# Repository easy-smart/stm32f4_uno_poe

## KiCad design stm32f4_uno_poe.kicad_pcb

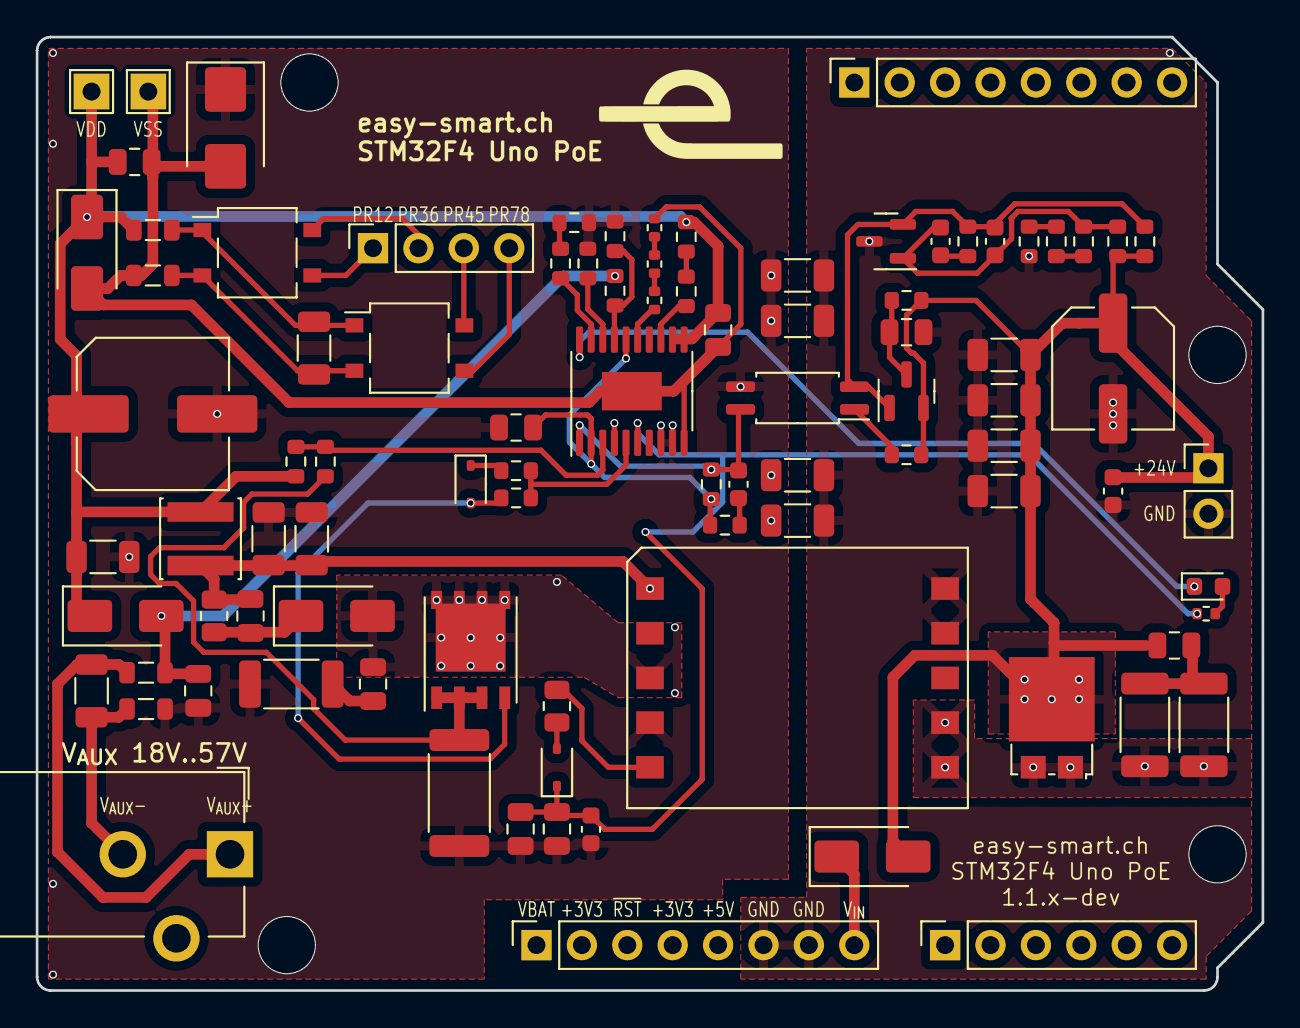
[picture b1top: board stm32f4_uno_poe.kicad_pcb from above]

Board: 2 copper layers, 68.6 x 53.3 mm, 95 parts (0 on the bottom side), 50 nets.

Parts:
C201, C228: 1u 50V; C_0805_2012Metric
C202: 47n 50V; C_0603_1608Metric
C203, C209, C217, C218, C220, C221: 1n 2kV; C_1206_3216Metric
C204, C210, C215, C225, C229: 100n 100V; C_0805_2012Metric
C205: 100p 50V; C_0603_1608Metric
C206: 22n 50V; C_0603_1608Metric
C207, C213, C214: 2u2 100V; C_1206_3216Metric
C211: 47u 63V; C_Elec_8x10.2
C216: 100p 500V; C_0805_2012Metric
C219, C232: 1u 50V; C_0603_1608Metric
C222: 330p 500V; C_0805_2012Metric
C223, C224, C226, C230: 4u7 50V; C_1206_3216Metric
C227: 22u 25V; C_0805_2012Metric
C231: 22u 63V; C_Elec_6.3x5.4
D101: SS210; D_SMA
D201: BAT54S; SOT-23
D202: SS220; D_SMA
D203, D204: MB10S; TO-269AA
D205: 1A 1kV 75ns; D_SMA
D206, D207: 1N4148WS; D_SOD-323
D208: 150V 10A; TO-277A
D209: 58V TVS; D_SMB
D210: LED green; LED_0603_1608Metric
D214: 58V TVS; D_SMA
J106: Power; PinSocket_1x08_P2.54mm_Vertical
J107: Conn_01x04; PinSocket_1x04_P2.54mm_Vertical
J109: STM32 GPIO; PinSocket_1x06_P2.54mm_Vertical
J110: Digital/PWM; PinSocket_1x08_P2.54mm_Vertical
J112: Barrel_Jack; CUI Devices PJ-102AH.pdf
J113: Conn_01x02; PinHeader_1x02_P2.54mm_Vertical
L201, L202, L203, L204: 600Ω@100MHz (500mA); L_0805_2012Metric
L205: 3u3; L_Sunlord_SWPA4030S
MH1, MH2, MH3, MH4: MountingHole_3.2mm
Q201: Si7450DP; PowerPAK_SO-8_Single
R201: 4k99; R_0603_1608Metric
R202, R207, R212, R218: 10k; R_0603_1608Metric
R203: 1k5; R_0603_1608Metric
R204: 6k04; R_0603_1608Metric
R205: 240k; R_0603_1608Metric
R206: 2k; R_0603_1608Metric
R208, R211: 49.9k; R_0603_1608Metric
R209: 20k; R_0603_1608Metric
R210: 22k; R_0603_1608Metric
R213: 220; R_0603_1608Metric
R214, R216: 470; R_0603_1608Metric
R215, R220: 470; R_0402_1005Metric
R217: 330; R_0402_1005Metric
R219: 15k; R_0603_1608Metric
R221: 39k; R_0805_2012Metric
R222: 100; R_0603_1608Metric
R223: 4E7; R_0603_1608Metric
R224: 1k; R_0603_1608Metric
R225: 274k; R_0603_1608Metric
R226: 0E12 1W; R_2512_6332Metric
R227: 75 750mW; R_2010_5025Metric
R228: 20; R_0805_2012Metric
R229, R230: 100 750mW; R_2010_5025Metric
R232: 4k7; R_0402_1005Metric
TP201: VDD; TestPoint_THTPad_2.0x2.0mm_Drill1.0mm
TP202: VSS; TestPoint_THTPad_2.0x2.0mm_Drill1.0mm
TR201: Coilcraft POE40Q-24E; Coilcraft POE40Q-xxE
U201: EL3H7(A)(TA)-G; SOP-4_4.4x2.6mm_P1.27mm
U202: CJ431; SOT-23
U203: TPS23754PWP; TSSOP-20-1EP_4.4x6.5mm_P0.65mm_EP2.15x3.35mm

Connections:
/PoE/+24V: C222.1, C223.1, C224.1, C226.1, C230.1, C231.1, C232.1, D101.2 (A), D201.2 (K), D208.3 (K), J113.1, R201.1, R202.1, R204.1, R207.1
/PoE/+V_SEC: D208.1 (A), D208.2 (A), R229.1, R230.1, TR201.6, TR201.7
/PoE/APD: R205.2, R210.1, U203.17 (APD)
/PoE/AUX: C204.1, D202.2 (A), L201.2, R205.1
/PoE/BLNK: R211.2, U203.18 (BLNK)
/PoE/CS: R224.2, R225.2, U203.3 (CS)
/PoE/CTL: C202.1, R206.2, U201.4, U203.1 (CTL)
/PoE/FRS: R208.2, U203.19 (FRS)
/PoE/GATE: R222.2, R223.2, U203.5 (GATE)
/PoE/PGND: C204.2, C207.2, C211.2, C213.2, C214.2, C219.2, C220.1, C221.1, C225.1, C227.2, C228.2, D209.1 (K), L202.2, R209.1, R210.2, R211.1, R226.2, R227.2, TR201.4, U201.3, U203.4 (COM), U203.8 (ARTN), U203.9 (RTN)
/PoE/PGND_S: Q201.1 (S), Q201.2 (S), Q201.3 (S), R224.1, R226.1
/PoE/PR12: D203.3, J107.1
/PoE/PR36: D203.4, J107.2
/PoE/PR45: D204.4, J107.3
/PoE/PR78: D204.3, J107.4
/PoE/T2P: D210.1 (K), U203.20 (T2P)
/PoE/VB: C225.2, R203.1, R206.1, U203.2 (VB), U203.16 (DT)
/PoE/VC: C219.1, C227.1, C228.1, D207.1 (K), R232.2, U203.6 (VC)
/PoE/VDD: C207.1, C210.1, C211.1, C229.1, D202.1 (K), D214.1 (K), L203.2, L205.1, R219.1, R225.1, TP201.1, U203.11 (VDD1), U203.12 (VDD)
/PoE/VDD_B: C209.1, D203.1 (+), D204.1 (+), L203.1
/PoE/VDD_PRI+: C213.1, C214.1, C215.1, C217.1, C218.1, L205.2, R221.1, TR201.1
/PoE/VDD_PRI-: C216.1, D205.2 (A), Q201.5 (D), TR201.3
/PoE/VDD_SN: C215.2, D205.1 (K), R221.2
/PoE/VSS: C210.2, C229.2, D209.2 (A), D214.2 (A), L204.2, R220.1, TP202.1, U203.10 (VSS_1), U203.21 (VSS_2)
/PoE/VSS_B: C209.2, D203.2 (-), D204.2 (-), L204.1
/PoE/V_{AUX}+: C203.1, J112.1, L201.1
/PoE/V_{AUX}-: C203.2, J112.2, L202.1
GND: C201.1, C217.2, C218.2, C220.2, C221.2, C223.2, C224.2, C226.2, C230.2, C231.2, C232.2, J106.6, J106.7, J113.2, R216.2, TR201.9, TR201.10, U202.3 (A)
unnamed: C202.2, R203.2
unnamed: C206.2, R212.2
unnamed: C216.2, R227.1
unnamed: C222.2, R229.2, R230.2
unnamed: D101.1 (K), J106.8
unnamed: C205.2, D201.1 (A), R204.2, R212.1, U201.2, U202.2 (K)
unnamed: C201.2, D201.3 (COM), R202.2
unnamed: D206.2 (A), Q201.4 (G), R222.1
unnamed: D206.1 (K), R223.1
unnamed: D207.2 (A), R228.2
unnamed: D210.2 (A), R232.1
unnamed: R201.2, U201.1
unnamed: R208.1, R209.2
unnamed: R213.2, R214.1
unnamed: R214.2, R216.1
unnamed: R215.1, R220.2
unnamed: R215.2, R217.1
unnamed: R218.1, R219.2
unnamed: R228.1, TR201.5
unnamed: C205.1, C206.1, R207.2, R213.1, U202.1 (REF)
unnamed: R217.2, U203.15 (CLS)
unnamed: R218.2, U203.13 (DEN)

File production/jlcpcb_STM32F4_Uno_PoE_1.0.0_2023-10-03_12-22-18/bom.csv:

Designator,Footprint,Quantity,Value,LCSC Part #
"C201, C228",0805,2,1u 50V,C28323
C202,0603,1,47n 50V,C1622
"C203, C209, C217, C218, C220, C221",1206,6,1n 2kV,C9196
"C204, C210, C215, C225, C229",0805,5,100n 100V,C28233
C205,0603,1,100p 50V,C14858
C206,0603,1,22n 50V,C21122
"C207, C213, C214",1206,3,2u2 100V,C170101
C211,C_Elec_8x10.2,1,47u 63V,C72524
C216,0805,1,100p 500V,C107122
"C219, C232",0603,2,1u 50V,C15849
C222,0805,1,330p 500V,C77468
"C223, C224, C226, C230",1206,4,4u7 50V,C29823
C227,0805,1,22u 25V,C45783
C231,C_Elec_6.3x5.4,1,22u 63V,C98744
D101,D_SMA,1,SS210,C14996
D201,SOT-23,1,BAT54S,C7420333
D202,D_SMA,1,SS220,C7420361
"D203, D204",TO-269AA,2,MB10S,C2488
D205,D_SMA,1,1A 1kV 75ns,C412437
"D206, D207",D_SOD-323,2,1N4148WS,C2128
D208,TO-277A,1,150V 10A,C2912069
D210,0603,1,LED green,C72043
D214,D_SMA,1,58V TVS,C115922
"L201, L202, L203, L204",0805,4,600Ω@100MHz (500mA),C1017
L205,L_Sunlord_SWPA4030S,1,3u3,C15269
Q201,PowerPAK_SO-8_Single,1,Si7450DP,C913434
R201,0603,1,4k99,C23046
"R202, R207, R212, R218",0603,4,10k,C25804
R203,0603,1,1k5,C22843
R204,0603,1,6k04,C2759712
R205,0603,1,240k,C4197
R206,0603,1,2k,C22975
"R208, R211",0603,2,49.9k,C23184
R209,0603,1,20k,C4184
R210,0603,1,22k,C31850
R213,0603,1,220,C22962
"R214, R216",0603,2,470,C23179
"R215, R220",0402,2,470,C25117
R217,0402,1,330,C25104
R219,0603,1,15k,C22809
R221,0805,1,39k,C25826
R222,0603,1,100,C22775
R223,0603,1,4E7,C23164
R224,0603,1,1k,C21190
R225,0603,1,274k,C22968
R226,2512,1,0E12 1W,C2934371
R227,2010,1,75 750mW,C172257
R228,0805,1,20,C17544
"R229, R230",2010,2,100 750mW,C171260
R232,0402,1,4k7,C25900
U201,SOP-4_4.4x2.6mm_P1.27mm,1,EL3H7(A)(TA)-G,C181879
U202,SOT-23,1,CJ431,C3113
U203,TSSOP-20-1EP_4.4x6.5mm_P0.65mm_EP2.15x3.35mm,1,TPS23754PWP,C181651

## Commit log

2023-09-11 Add flyback transformator
2023-09-12 More reference designs
2023-09-14 Add ETH_RXER
2023-09-14 Set DNP
2023-09-20 #1 Use new central library KiCad-Lib
2023-09-28 PCB ready
2023-10-02 #2 Add silkscreen texts
2023-10-02 #3 Match pcb to ethernet and base
2023-10-03 Release 1.0.0 sent to JLCPCB
2023-10-03 PCB production confirmed
2023-10-13 Update library. Coilcraft orientation was wrong.
2023-10-14 Add product photos
2023-10-16 Add measurement
2023-10-17 Add workflow
